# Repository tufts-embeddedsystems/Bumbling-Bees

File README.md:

# Bumbling-Bees

Contributors: Max Ramer, Brandon Gray, Melinda Burns, Alina Shah, Arnav Gupta, Muheng Shen

## Goal

Design, build, and program 10 temperature sensor nodes to measure temperature once an hour.  Nodes should last 6 months in the field.

## Roles

Hardware Engineers: Muheng & Arnav

Firmware Engineers: Brandon & Max

Software Engineers: Mels & Alina

## Tasks

#### Hardware

- [ ] Create an acceptance testing plan. Must test:
  
  - [ ] Sensor and thermistor
  
  - [ ] Remaining battery life
  
  - [ ] WiFi capability

- [ ] Build 1 PCB dev board

- [ ] Verify dev board functionality with testing plan

- [ ] Build and test 10 PCB dev boards

#### Firmware

- [ ] Design main program execution loop

- [ ] Collaborate with software team to finish demos

- [ ] Collaborate with hardware team to develop acceptance tests using software team demos

#### Software

- [ ] Finalize demos with firmware team:
  
  - [ ] Sensor and thermistor
  
  - [ ] Remaining battery life
  
  - [ ] WiFi & MQTT

- [ ] Write program execution loop

- [ ] Setup web server-side HTML to test MQTT messages

## 

## File structure

- `hardware/`
  
  - `pcb/`
    
    - `devboard_final/`: all KiCad files for development of the temperature node PCB. Also includes Gerber files.
  
  - `testing_plan/`: documentation for acceptance tests necessary to ensure correct PCB design.

- `PlatformIO/`: necessary files for dev environment

- `software/`
  
  - `demo/`: all code to demo individual functionality (i.e. measure temperature, connect to WiFi, enter deep sleep)
  
  - `libs/`: any necessary libraries for development
    
    `main/`: main program execution code for a node. Encompasses all demos.

## Program Execution

## Status Updates

#### Tuesday 4/26

#### Thursday 4/28

#### ...

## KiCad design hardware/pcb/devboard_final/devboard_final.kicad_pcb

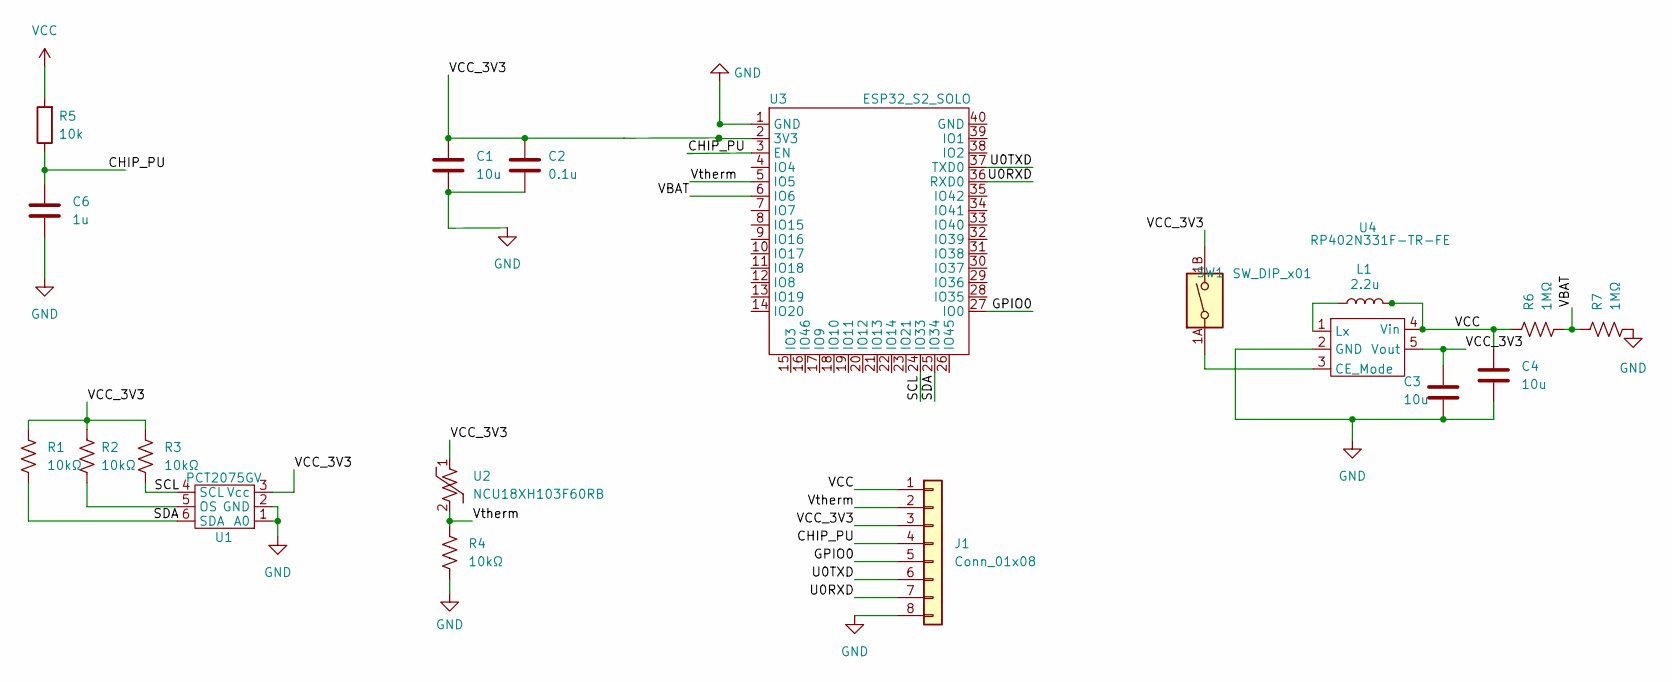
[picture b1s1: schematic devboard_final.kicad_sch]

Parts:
C1, C3, C4: 10u; C_0805_2012Metric_Pad1.18x1.45mm_HandSolder
C2: 0.1u; C_0805_2012Metric_Pad1.18x1.45mm_HandSolder
C6: 1u; C_0805_2012Metric_Pad1.18x1.45mm_HandSolder
J1: Conn_01x08; PinHeader_1x08_P2.54mm_Vertical
L1: 2.2u; L_0805_2012Metric_Pad1.05x1.20mm_HandSolder
R1, R2, R3, R4: 10kΩ; R_0805_2012Metric_Pad1.20x1.40mm_HandSolder
R5: 10k; R_0805_2012Metric_Pad1.20x1.40mm_HandSolder
R6, R7: 1MΩ; R_0805_2012Metric_Pad1.20x1.40mm_HandSolder
SW1: SW_DIP_x01; SW_DS04-254-1-01BK-SMT
U1: PCT2075GV; TSOP-6_1.65x3.05mm_P0.95mm
U2: NCU18XH103F60RB; R_0805_2012Metric_Pad1.20x1.40mm_HandSolder
U3: ESP32_S2_SOLO; ESP-32-S2-SOLO
U4: RP402N331F-TR-FE; SOT-23-5

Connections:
/CHIP_PU: C6.1, J1.4, R5.1, U3.3 (EN)
/GPIO0: J1.5, U3.27 (IO0)
/SCL: R3.2, U1.4 (SCL), U3.24 (IO33)
/SDA: R1.2, U1.6 (SDA), U3.25 (IO34)
/U0RXD: J1.7, U3.36 (RXD0)
/U0TXD: J1.6, U3.37 (TXD0)
/VBAT: R6.2, R7.1, U3.6 (IO6)
/VCC_3V3: C3.2, J1.3, R1.1, R2.1, R3.1, SW1.1B, U1.3 (Vcc), U2.1, U4.5 (Vout)
/Vtherm: J1.2, R4.1, U2.2, U3.5 (IO5)
GND: C1.2, C2.2, C3.1, C4.2, C6.2, J1.8, R4.2, R7.2, U1.1 (A0), U1.2 (GND), U3.1 (GND), U4.2 (GND)
unnamed: C1.1, C2.1, U3.2 (3V3)
unnamed: L1.1, U4.1 (Lx)
unnamed: R2.2, U1.5 (OS)
unnamed: SW1.1A, U4.3 (CE_Mode)
VCC: C4.1, J1.1, L1.2, R5.2, R6.1, U4.4 (Vin)

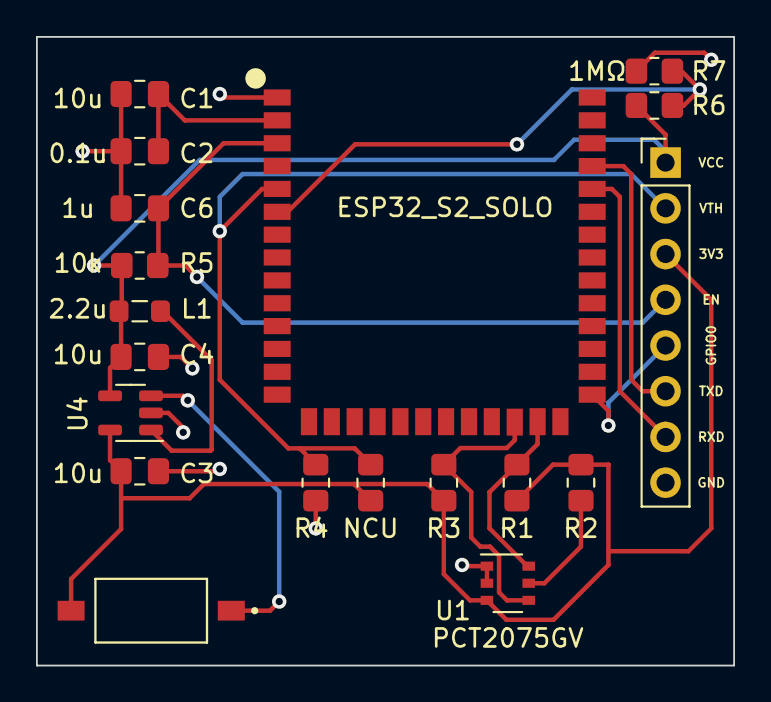
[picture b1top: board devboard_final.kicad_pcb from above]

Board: 2 copper layers, 38.7 x 34.9 mm, 19 parts (0 on the bottom side), 15 nets.

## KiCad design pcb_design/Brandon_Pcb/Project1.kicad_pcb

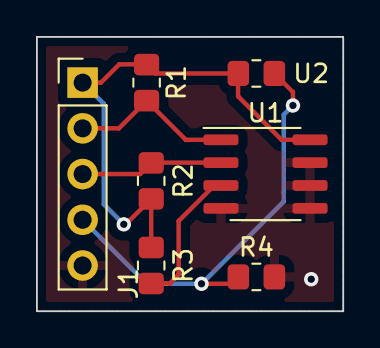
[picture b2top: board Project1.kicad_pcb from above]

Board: 2 copper layers, 17.0 x 15.2 mm, 7 parts (0 on the bottom side), 6 nets.

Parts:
J1: Conn_01x05; PinHeader_1x05_P2.54mm_Vertical
R1, R2, R3: 1kΩ; R_0805_2012Metric_Pad1.20x1.40mm_HandSolder
R4: 13kΩ; R_0805_2012Metric_Pad1.20x1.40mm_HandSolder
U1: AT30TS74; SOIC-8_3.9x4.9mm_P1.27mm
U2: NCU18XH103F60RB; R_0805_2012Metric_Pad1.20x1.40mm_HandSolder

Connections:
/SCL: J1.3, R2.2, U1.2 (SCL)
/SDA: J1.2, R1.2, U1.1 (SDA)
/Vtherm: J1.4, R4.1, U2.2
GND: J1.5, R4.2, U1.4 (GND), U1.5 (A2), U1.6 (A1), U1.7 (A0)
unnamed: R3.2, U1.3 (ALERT)
VCC: J1.1, R1.1, R2.1, R3.1, U1.8 (Vcc), U2.1

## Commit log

2022-04-11 added comments and organization
2022-04-12 Updated ESP32-S2 chip
2022-04-12 Added voltage regulator to schematic
2022-04-13 finalized PCB
2022-04-13 Finalized schematic
2022-04-13 Added Programming board
2022-04-13 v1 of PCB layout done
2022-04-21 organized file structure, added descriptive README
2022-04-21 added placeholders so that ddirectories show up on github
2022-04-21 added placeholder
2022-04-21 added new directory
2022-04-21 Added program_flow_diagram.drawio
2022-04-21 changed name of diagram file
2022-04-21 Added program_flow_diagram.drawio.svg
2022-04-21 one more README edit
2022-04-21 one more README edit but fo rreal
2022-04-26 Wifi code
    Added wifi code in software/demo/wifi_mqtt
2022-04-26 Deleted extra files
2022-04-27 Wifi + MQTT + deep sleep loop
2022-04-27 Trying some stuff
2022-04-29 Fixed MQTT!!
    yay
2022-05-04 Changed test battery level
2022-05-05 Final code
    Long live the bumbling bees
2022-05-05 Added MAC finder and changed sleep time to 1 hr
